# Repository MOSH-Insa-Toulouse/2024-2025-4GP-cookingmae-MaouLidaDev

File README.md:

# 2024-2025-4GP-cookingmae-MaouLidaDev

# SOMMAIRE
***
- [2024-2025-4GP-cookingmae-MaouLidaDev](#2024-2025-4gp-cookingmae-maoulidadev)
- [SOMMAIRE](#sommaire)
    - [But du projet](#but-du-projet)
    - [Livrables](#livrables)
    - [Matériel donnée](#matériel-donnée)
    - [Simulation du circuit sous Ltspice](#simulation-du-circuit-sous-ltspice)
    - [Création du Shield sous Kicad](#création-du-shield-sous-kicad)
    - [Code Arduino](#code-arduino)
    - [Application Android sous MIT App Inventor](#application-android-sous-mit-app-inventor)
    - [Banc de test](#banc-de-test)
    - [Datasheet](#datasheet)
    - [Conclusion](#conclusion)
    - [Contact](#contact)
***  

### But du projet

Le but du projet est de pouvoir venir comparer deux technologies de jauge de contrainte.
* Une jauge provenant du commerce : Un "flex sensor" ayant une résistance à plat d'environ 28KOhms
* Une jauge de contrainte en graphite faite par nos soins s'inscrivant dans le cadre des technologies low tech

Pour fabriquer notre jauge de contrainte low tech et low cost, nous nous basons sur un article scientifique intitulé: "Pencil Drawn Strain Gauges and Chemiresistors on Paper" publié par Cheng-Wei Lin, Zhibo Zhao, Jaemyung Kim et Jiaxing Huang dans lequel il a été prouvé que l'on puisse créer une jauge de contraite à partir d'une piste de graphite. Cette piste de graphite peut être dessiner à l'aide d'un crayon à papier sur une feuille de papier tout deux disponibles dans le commerce. En effet, en se basant sur les phénomènes de transport dans les systèmes granulaires, on peut observer une modification de la resistance de la piste en fonction de la flexion de cette dernière. Nous souhaitons observer ce phénomène pour differentes pistes de graphite plus au moins chargées en particles de graphite. Ainsi, nous pourrons étudier la variation de résistance de la piste en fonction de la déformation et ce pour chaque piste obtenue par dépot de crayon à papier differents.

Afin de pouvoir observer ce phénomène, nous avons débuté ce projet et proposons de répondre à la question suivante: "Est ce que la sensibilité d'une jauge de contrainte en graphite peut être comparable à celle d'une jauge dans le commerce et si oui est-il possible de commercialiser cette jauge low cost et low tech à grande echelle?"

Pour repondre à cette question, nous mettons en place un protocole constituer de phase de design, création, programmation et test pour notre jauge de contrainte en graphite.
Voici  un récapitulatif des étapes:
* Designer et créer un montage d'amplifaction nous permettant d'exploiter notre jauge en graphite et de relier sa sortie à une carte arduino
* Intégrer un potentiomètre digitale en entrée de notre montage d'amplifaction pour calibrer les mesures
* Créer un shield sous Kicad permettant d'y intégrer notre montage amplificateur, notre potentiomètre, nos 2 capteurs à comparer, un écran OLED pour voir la mesure que nous effectuons, un module Bluetooth pour exporter les datas vers un téléphone android et un encodeur rotatoire
* Préparer le PCB et y integrer tous les composants 
* Créer un code Arduino nous permettant de contrôler tous les éléments dont nous disposons sur notre PCB
* Tester notre code ainsi que notre montage physique 
* Tester les deux capteurs et recenser dans une datasheet les caractéristiques de notre jauge de contrainte low cost
* Répondre à la problèmatique concernant notre jauge de contrainte 
* Préparer nos splendides résultats durant une soutenance fin Mai

### Livrables

* Un shield PCB conçu sous Kicad pouvant se fixer à une carte Arduino UNO avec au-dessus un amplificateur transimpédance, un module Bluetooth, un écran OLED, un potentiomètre digital, un encodeur rotatoire, un Flex Sensor et notre capteur.
* Un code Arduino gérant la mesure de résistance d'une jauge de contrainte faite en graphite, la communication avec un module Bluetooth pour réceptionner les valeurs de la mesure sur un portable Android, l'affichage sur l'écran OLED d'actions possibles et la gestion du potentiomètre digital permettant la calibration de notre capteur.
* Un code Android APK qui gère l'interfaçage du système de mesure sur un téléphone Android.
* La datasheet du capteur de contrainte en graphite.

### Matériel donnée 

* 1 carte Arduino Uno
* 2 Résistance de 100kΩ
* 1 Résistance de 1kΩ
* 1 Potentiomètre digital MCP-41050
* 2 Condensateurs 100nF
* 1 Condensateurs 1µF
* 1 AOP LTC1050
* 1 Écran OLED01
* 1 Module Bluetooth HC-05

### Simulation du circuit sous Ltspice

Nous souhaitons pouvoir récupérer la resistance de notre capteur de Graphite. Ce dernier, lorsqu'une de ses pins est connectée à une source de tension d'environ 5V, délivre sur sa deuxième pin un très faible courant (de l'ordre du nanoampère). En effet, la résistance de notre jauge de contrainte en graphite est de l'ordre du gigaohm ce qui pour la gamme de tension d'alimentation dont nous disposons pour nos tests se traduit par un courant très faible à exploiter. 

Pour pouvoir tout de même récupérer la variation de resistance de notre capteur, nous proposon un montage d'amplification transimpédence composé de 3 filtres passe bas et d'un AOP. L'AOP amplifie notre signal pour atteindre une tension qui pourra ensuite être lue par une carte Arduino UNO. Nous avons choisi le LTC 1050.
En plus de l'AOP, nous rajoutons 3 filtres: 
  - Un filtre passe bas passif composé de R1 et C1 de fréquence de coupure de 16Hz pour filtrer les bruits en courant sur le signal d'entrée
  - Une filtre passe bas actif composé de R3 et C4 de fréquence de coupure de 1.6Hz permettane de filtre la composante de bruit à 50Hz provenant du couplage avec le réseau éléctrique 
  - Un filtre passe bas standard composé de R6 et C2 de fréquence de coupure de 1.6kHz qui permet de s'affranchir des bruit crées par l'environnement de l'observation
 Il est possible de venir rajouter une resistance variable R2 de sorte à pouvoir garantir la non saturation de l'entrée analogique de la carte Arduino UNO récupérant le signal de sortie de l'amplificateur transimpédance. En effet, comme la resistance de la piste varie en fonction de sa teneur en particule de graphite, il sera possible de venir faire varier R2 pour modifier le gain de notre amplification. 
 
 Nous avons testé ce montage sur le logiciel LTspice basé sur [ce schéma](https://github.com/MOSH-Insa-Toulouse/2024-2025-4GP-cookingmae-MaouLidaDev/blob/main/Images/SchemaLTSpice.png) 

Grâce à notre simulation, nous avons pu valider que nos filtres sont bien dimensionnés pour atténuer les bruits (par exemple, dans le cas des simulations en courant alternatif, on constate que notre atténuation est de l'orde 40dB pour la composante à 50Hz).

### Création du Shield sous Kicad

Voici ci-dessous des images des schéma de notre PCB sous Kicad: 

Le PCB a été entierement designé sous le logiciel Kicad et imprimé au sein de deux départements de l’INSA Toulouse, le Génie Électrique et Informatique et le Génie Physique. Il a été fabriqué avec une plaquette d’époxy recouverte d’une couche de cuivre d’environ 60𝝻m sur laquelle nous avons imprimé le circuit. Pour imprimé le circuit, nous utilisons un calque nous permettant d'isoler les pistes des UVs et de venir graver à l'aide d'un bain de percholorure de fer les parties en cuivre non désirées. 

Une fois le PCB tiré, nous sommes passé à la soudure des composants nécéssaires pour pouvoir analyser la réponse de notre capteur graphite. 
Voici ci-dessous une image de notre carte une fois imprimée et une fois tous les composants ajoutés: 

### Code Arduino 

Pour pouvez retrouver le code commenté permettant d'avoir la variation de résistance relative en fonction de la déformation [ici](https://github.com/MOSH-Insa-Toulouse/2024-2025-4GP-cookingmae-MaouLidaDev/blob/main/Arduino/Code_Arduino.ino)

Le but de ce code est de gérer l'acquisition des tensions en sortie de l'amplificateur et du Flex Sensor, ainsi que la calibration automatique du potentiomètre digital.

Lorsque le code est téléversé sur la carte Arduino, le programme attend que le début de l'acquisition soit enclenché par l'utilisateur sur l'application Android (mentionnée plus tard). Après cette première étape, il est possible de sélectionner plusieurs actions en tournant et en appuyant sur l'encodeur rotatoire :\
-Pause qui force le programme à ne rien faire;\
-Calibre A qui calibre le potentiomètre digital pour que la tension en sortie de l'AOP ne sature pas à 5V ou à 0V;\
-Mesure Flex qui récupère la valeur de la tension sur le Flex Sensor et la convertit en résistance, mesure envoyée à l'application Android sous forme de byte;\
-Mesure Capteur qui récupère la valeur de la tension en sortie de l'AOP et envoie la donnée à l'application Android sous forme de byte;

La fréquence d'échantillonage est de 2Hz (pour Mesure Flex et Capteur). Lors que l'action Calibre A est sélectionnée, le programme n'effectue que cette tâche et aucune autre fonction est activée. Cette calibration prend entre 5 et 10s.

### Application Android sous MIT App Inventor

Pour pouvoir récupérer la variation de la résistance en fonction de la déformation, nous avont créer une application pouvant communiquer avec le module Bluetooth présent sur notre PCB. Nous avons utilisé le site MIP App Inventor. 
Vous retrouverez notre application dans la séction dédiée. Nous avons : 

Le but de ce code est de gérer la réception des données et de leur affichage, ainsi que la calibration manuelle pour initialiser la résistance variable R2.

Lorsqu'on se connecte au module Bluetooth présent sur la PCB, on peut commencer l'acquisition des données. En fonction de l'action sélectionnée, on affiche sur la face-avant de l'application différentes informations. Si l'action sélectionée est :\
    -Pause, rien de nouveau s'affiche;\
    -Calibre A, il est nécéssaire d'appuyer sur le bouton "Calibration Automatique" pour récupérer la valeur de la résistance du potentiomètre digital. L'application reste figé et attend de recevoir de l'Arduino le byte associé au potentiomètre digital et affiche la valeur de la résistance et précise aussi que la calibration a été faite automatiquement;\
    -Mesure Flex, la valeur de la résistance est affiché dans un indicateur et sur un graphe pour suivre l'évolution de cette résistance. Il est nécessaire de placer le Switch du côté "Flex Sensor" pour avoir la bonne résistance du Flex Sensor;\
    -Mesure Capteur, la valeur de la résistance est affiché dans un indicateur et sur un graphe pour suivre l'évolution de cette résistance. Il est nécessaire de placer le Switch du côté "Capteur" pour avoir la bonne résistance du Capteur;

De plus, il est possible de rentrer manuellement la valeur de la résistance R2 si : la calibration automatique ne renvoie pas la bonne valeur mesurée sur le potentiomètre digital à l'aide d'un multimètre OU si on n'utilise pas de potentiomètre digital et qu'on le remplace simplement par une résistance. Enfin, il est possible d'arrêter l'acquisition des mesures et de la relancer, effaçant toutes les informations présentes sur le graphe et les indicateurs.

(Remarque : la fréquence du code Android est de 10Hz pour récupérer le byte de données associé aux résistances du Capteur et du Flex Sensor).

### Banc de test

Pour pouvoir compléter notre datasheet, nous devons évaluer les performances de notre capteur à travers un banc de test. Pour cela, nous utiliserons un demi cylindre à rayon variable dont nous connaissons préalablement le rayon de courbure: 

Ce banc de test a été imprimé en 3D et dispose de demis-cercles de rayons variant de 2cm à 4,5cm avec un pas de 0,5cm par demi cercle.  

Pour évaluer notre capteur en graphite, on veut pouvoir connaître la variation de résistance relative du capteur en fonction de la déformation subie. Nous notons la variation de résistance relative: $\frac{\Delta R}{R_0}$  et la déformation:  $\epsilon=\frac{e}{D}$ avec ${e}$ l'épaisseur de notre papier que l'on a mesurée à e=0.2mm et ${D}$ le diamètre du cercle choisit. Il est ainsi aisé de determiner la déformation associée à chaque demi-cercle et il ne reste plus que à mesurer la résistance ${R_0}$ de notre capteur au repos et la variation de résistance de ce dernier lorsqu'on vient le plaquer contre les différents demis-cercles. 

Nous souhaitions originalement utiliser cette méthode qui nous a été suggerée en cours mais il a été compliqué pour nous de la mettre en oeuvre. En effet, nous n'avions pas assez de variation en résistance pour les différents diamétres testés. Cela est peut être dû à un mauvais réglage du potentiomètre digitale ne nous permettant pas d'exploiter la sensibilité de la jauge. Nous passons à un test plus "rudimentaire" se basant sur le même principe mais sur lequel nous contrôlons cette fois l'angle d'inflexion (en rad) de la jauge. On a donc  $R=\frac{D}{2}=\frac{L}{\theta}$ avec L la longueur de notre jauge mesurée à L=3.8cm
Au final on peut écrire la déformation:  $\epsilon=\frac{e\theta}{2L}$

On obtient ainsi la courbe de la variation de résistance en fonction de la déformation. Nous testons notre capteur pour differentes compositions en particule de graphite en compression et aussi en tension. On note que lorsque la déformation est positive c'est que nous étudions la compression (l'angle de courbure est compté positif) alors que lorsqu'elle est négative c'est que nous étudions la tension (l'angle de courbure est compté négatif). 
Nous obtenons: 

De même, nous pouvons établir uniquement en tension cette fois ($\epsilon$ < 0), la courbe de variation de resistance du capteur commercial : "le flex sensor". Nous obtenons: 

De nos observations, on constate que la résistance diminue lorsque nous sommes en compression, ce qui est normal car les particules de graphites se rapprochent les unes des autres et permettent une meilleure conductivité. Logiquement, en tension, la résistance augmente puisque qu'on rend la distance entre chaque particule de graphite beaucoup plus grande. 
On constate aussi que ces variations de résistance dépendent beaucoup du niveau de gras du grain en graphite que nous avons utilisé pour notre jauge. Lorsque notre crayon comporte beaucoup de graphite (2B ou B), la variation relative de resistance est plus importante. Lorsque notre crayon est plus dur (HB 2H avec beaucoup d'argile et moins de graphite) la resistance à plat est plus importante et nous avons une variation relative de resistance moins importante.  

NB: Il y'a certaines zones d'incertitudes à prendre en compte lors de l'analyses des performances de nos capteurs. En effet, entre chaque capteur testé, il est impossible d'estimer réellement la quantité de graphite déposée. De plus, il est difficile d'estimer si le banc de test élaboré permet de tester sans dégrader la qualité de nos capteurs. Il serait ainsi intéressant d'élaborer un nouveau banc de test utilisant un servo-moteur. 

### Datasheet 

Pour pouvez retrouver la datasheet [ici](https://github.com/MOSH-Insa-Toulouse/2024-2025-4GP-cookingmae-MaouLidaDev/blob/main/Datasheet/Datasheet_capteur_2025.pptx)

### Conclusion

Le but de ce projet était de venir comparer une technologie de jauge de contrainte commerciale: "Flex sensor" avec une jauge de contrainte facilement reproductible et low cost en graphite se basant sur l'article : "Pencil Drawn Strain Gauges and Chemiresistors on Paper" publié par Cheng-Wei Lin, Zhibo Zhao, Jaemyung Kim et Jiaxing Huang.  

Notre problématique était la suivante: "Est ce que la sensibilité d'une jauge de contrainte en graphite peut être comparable à celle d'une jauge dans le commerce et si oui est-il possible de commercialiser cette jauge low cost et low tech à grande échelle?"

--> Notre jauge de contrainte en graphite permet en effet d'observer une variation de résistance en fonction de la déformation et assure donc sa mission de base. On peut appliquer sur nos jauges des tensions mais aussi des compressions ce qui n'est pas possible pour le capteur commercial Flex sensor dont nous disposons. Nos jauges en graphite permettent de plus grande variations de résistance que le flex sensor mais elles restent tout de même moins sensibles. Nous avons du mal à évaluer la flexion maximale que nous pouvons appliquer sur nos jauges donc nous ne pouvons pas déterminer si nous les cassons en cours d'expérimentation. Le flex sensor semble alors plus robuste et plus précis. 
Pour conclure, nos jauges en graphite low tech permettent d'avoir une idée sur la déformation grâce à une variation relative, ils sont faciles à produire et permettent d'exploiter le phénomène de conduction dans les systèmes granulaires et c'est assez cool! En revanche, ses performances sont limitées et sa sensibilité ne permet pas d'avoir des résultats similaires à ce qui se fait sur le marché. 

--> En ce qui concerne la commercialisation de notre capteur, nous venons de voir que les performances de notre jauges ne sont pas comparables à ce qui se fait sur le marché actuellement mais peut tout de même dépané et permettre de se faire une idée de la déformation. Malheureusement, nos conditions de test étant assez rudimentaires, nous ne pouvons pas attester de la qualité de notre produit. Afin de pouvoir pleinement répondre à cette question, il faudrait mener des tests plus reproductibles, plus en profondeur pour pouvoir atteindre de meilleures performances. 

### Contact

-Hamadi Maoulida: mhamadi@insa-toulouse.fr  
-Tartera Maëlys : tartera@insa-toulouse.fr

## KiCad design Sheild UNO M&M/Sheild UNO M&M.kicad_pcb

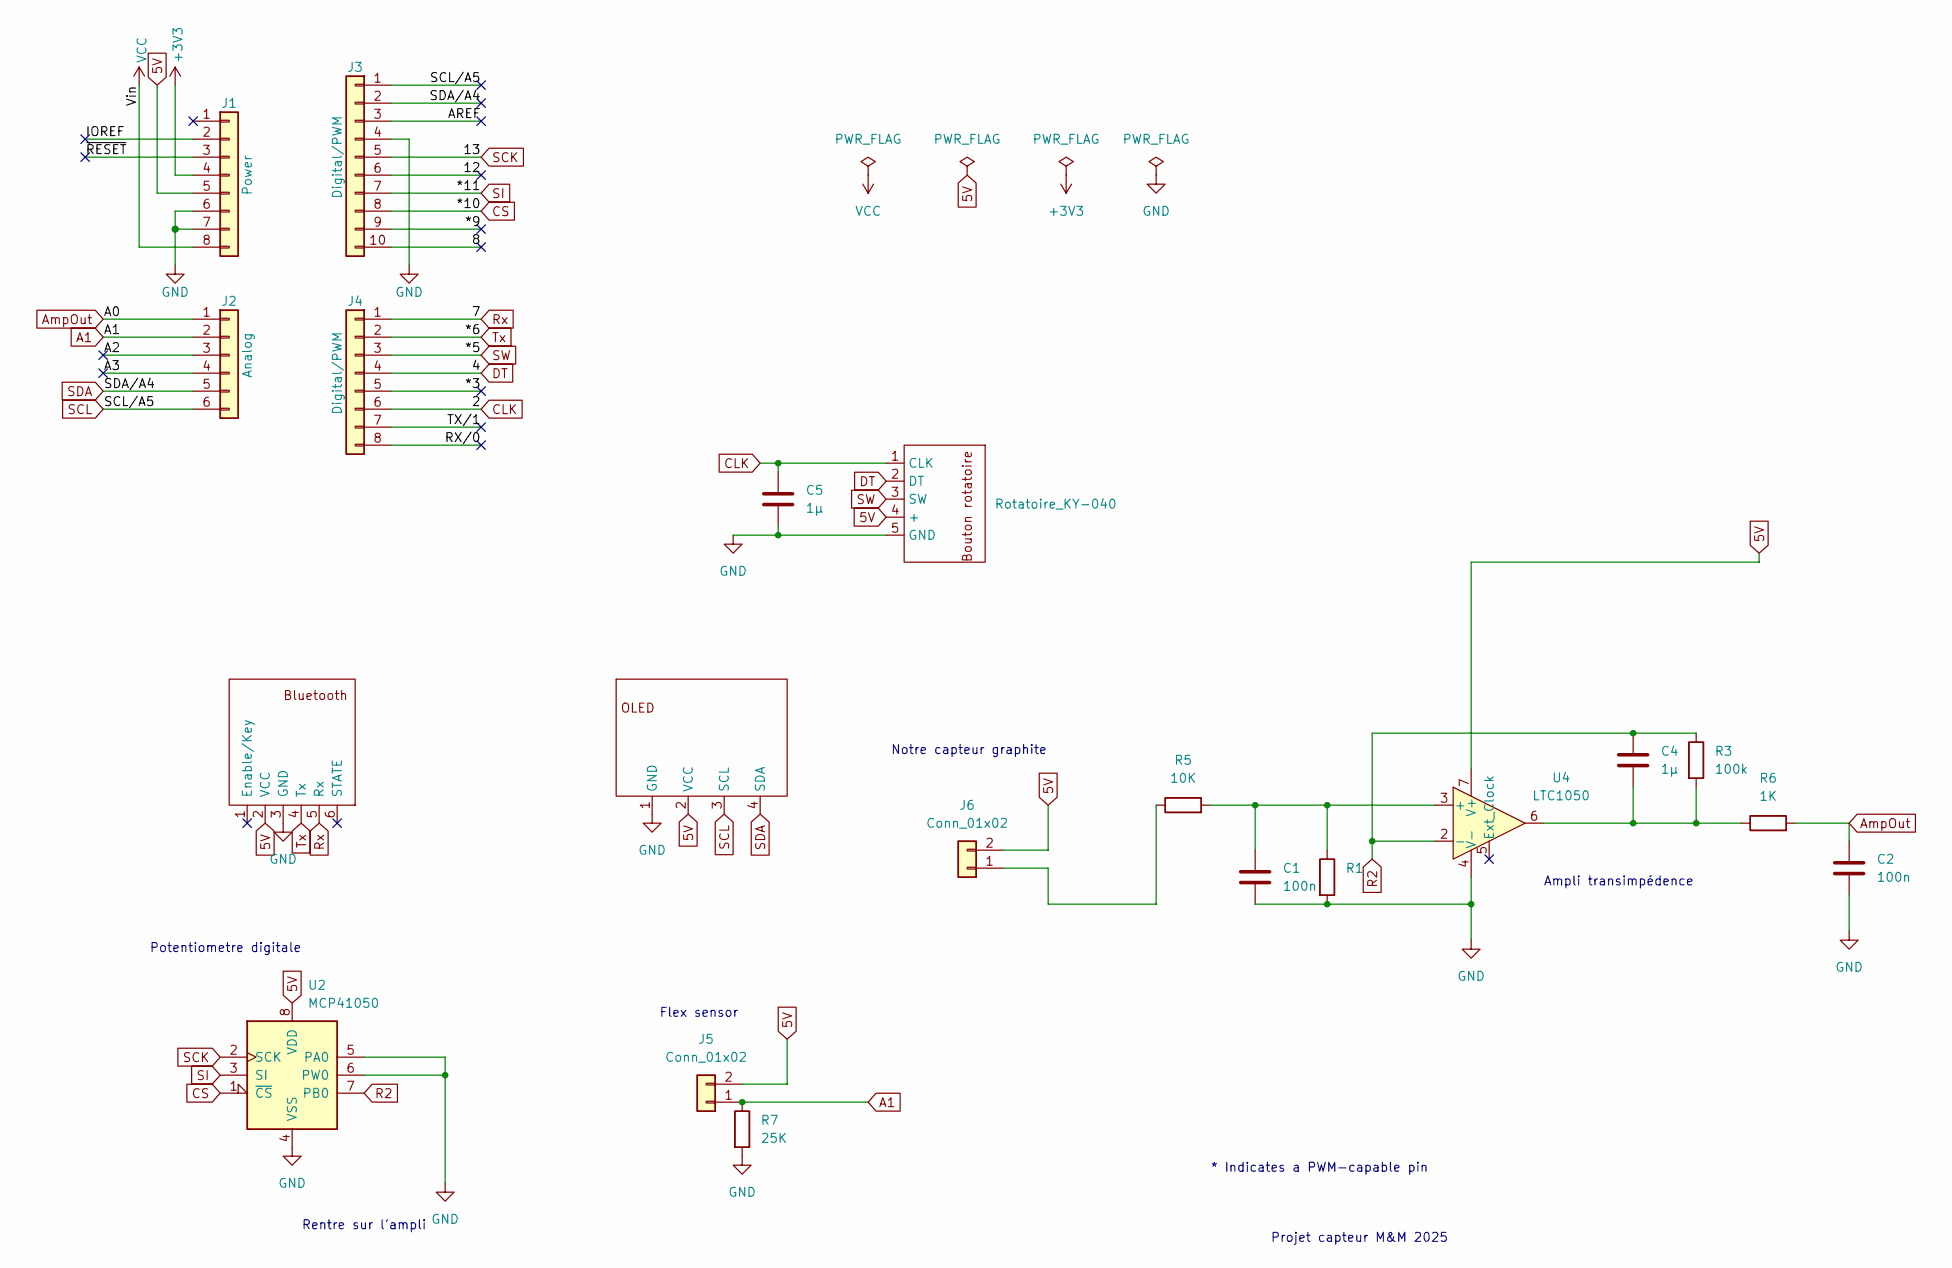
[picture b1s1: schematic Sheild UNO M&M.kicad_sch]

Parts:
1: Rotatoire_KY-040; Rotatoire_KEY-040_Empreinte
C1, C2: 100n; C_Disc_D6.0mm_W4.4mm_P5.00mm_Capa_100n_Empreinte
C4, C5: 1µ; C_Rect_L7.0mm_W4.5mm_P5.00mm_Capa_1µ_Empreinte
DS1: OLED; Oled_Empreinte
J1: Power; PinSocket_1x08_P2.54mm_Vertical
J2: Analog; PinSocket_1x06_P2.54mm_Vertical
J3: Digital/PWM; PinSocket_1x10_P2.54mm_Vertical
J4: Digital/PWM; PinSocket_1x08_P2.54mm_Vertical
J5, J6: Conn_01x02; PinSocket_1x02_P2.54mm_Vertical_Modifié
R1, R3: 100k; Resistance_Empreinte
R5: 10K; Resistance_Empreinte
R6: 1K; Resistance_Empreinte
R7: 25K; Resistance_Empreinte
U1: HC05; Blutooth_Empreinte
U2: MCP41050; Potentiometre MCP41050
U4: LTC1050; Potentiometre MCP41050

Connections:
5V: 1.4 (+), DS1.2 (VCC), J1.5, J5.2, J6.2, U1.2 (VCC), U2.8 (VDD), U4.7 (V+)
+3V3: J1.4
/8: J3.10
/12: J3.6
/*3: J4.5
/*9: J3.9
/A2: J2.3
/A3: J2.4
/AREF: J3.3
/IOREF: J1.2
/RX/0: J4.8
/TX/1: J4.7
/~RESET: J1.3
A1: J2.2, J5.1, R7.1
AmpOut: C2.1, J2.1, R6.2
CLK: 1.1 (CLK), C5.1, J4.6
CS: J3.8, U2.1 (~CS)
DT: 1.2 (DT), J4.4
GND: 1.5 (GND), C1.2, C2.2, C5.2, DS1.1 (GND), J1.6, J1.7, J3.4, R1.2, R7.2, U1.3 (GND), U2.4 (VSS), U2.5 (PA0), U2.6 (PW0), U4.4 (V-)
unnamed: C4.2, R3.2, R6.1, U4.6
unnamed: J6.1, R5.1
unnamed: C1.1, R1.1, R5.2, U4.3 (+)
R2: C4.1, R3.1, U2.7 (PB0), U4.2 (-)
Rx: J4.1, U1.5 (Rx)
SCK: J3.5, U2.2 (SCK)
SCL: DS1.3 (SCL), J2.6, J3.1
SDA: DS1.4 (SDA), J2.5, J3.2
SI: J3.7, U2.3 (SI)
SW: 1.3 (SW), J4.3
Tx: J4.2, U1.4 (Tx)
VCC: J1.8

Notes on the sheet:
Potentiometre digitale
Flex sensor
Projet capteur M&M 2025
Rentre sur l'ampli
* Indicates a PWM-capable pin
Ampli transimpédence
Notre capteur graphite

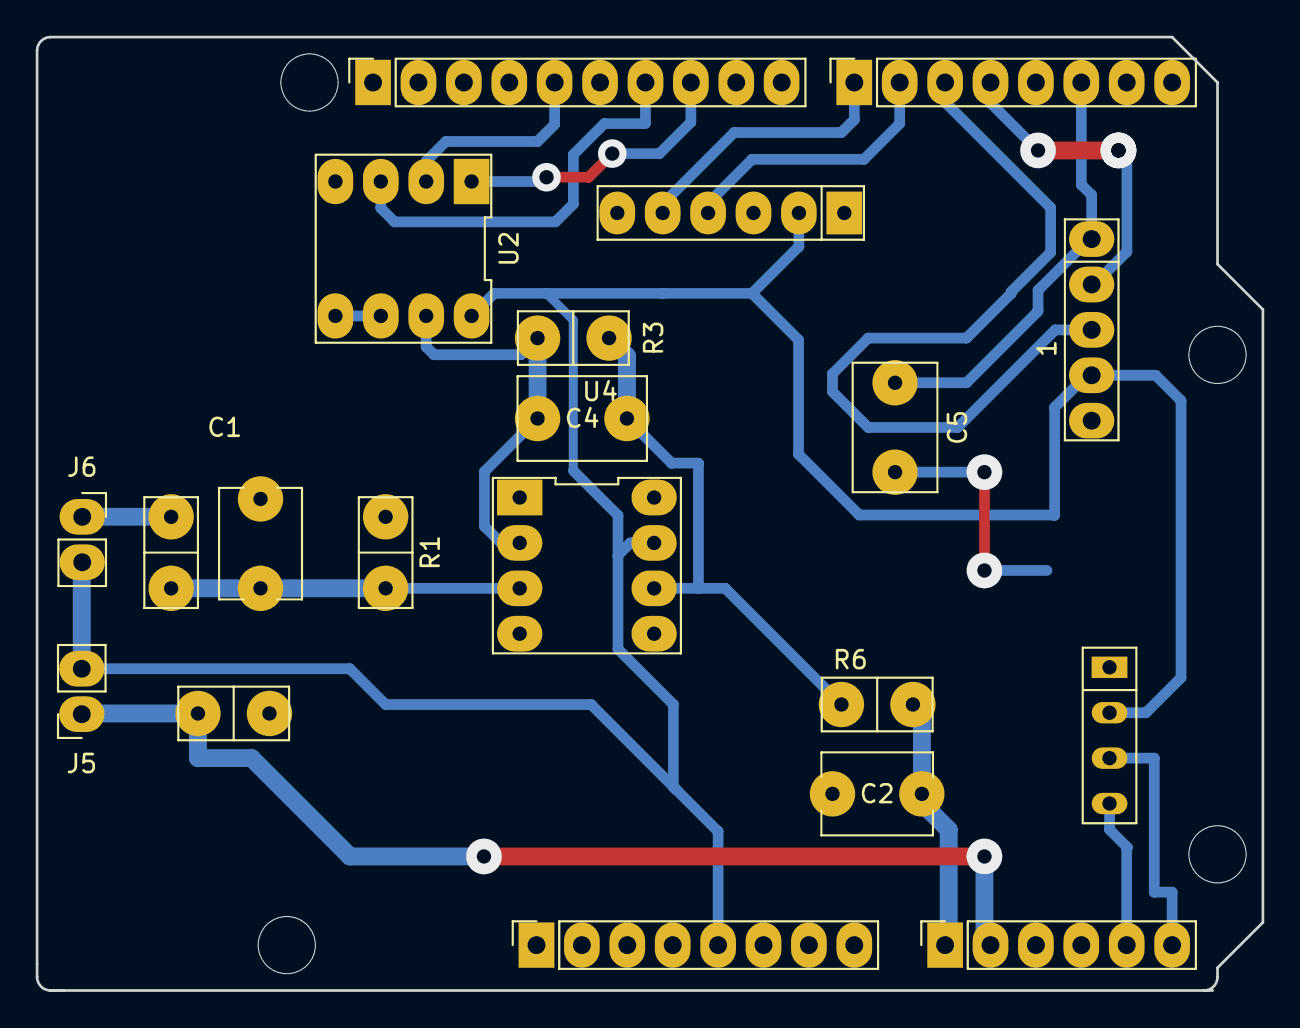
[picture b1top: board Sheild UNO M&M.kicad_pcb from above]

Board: 2 copper layers, 68.6 x 53.3 mm, 24 parts (0 on the bottom side), 18 nets.

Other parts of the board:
MH1, MH2, MH3, MH4: MountingHole_3.2mm

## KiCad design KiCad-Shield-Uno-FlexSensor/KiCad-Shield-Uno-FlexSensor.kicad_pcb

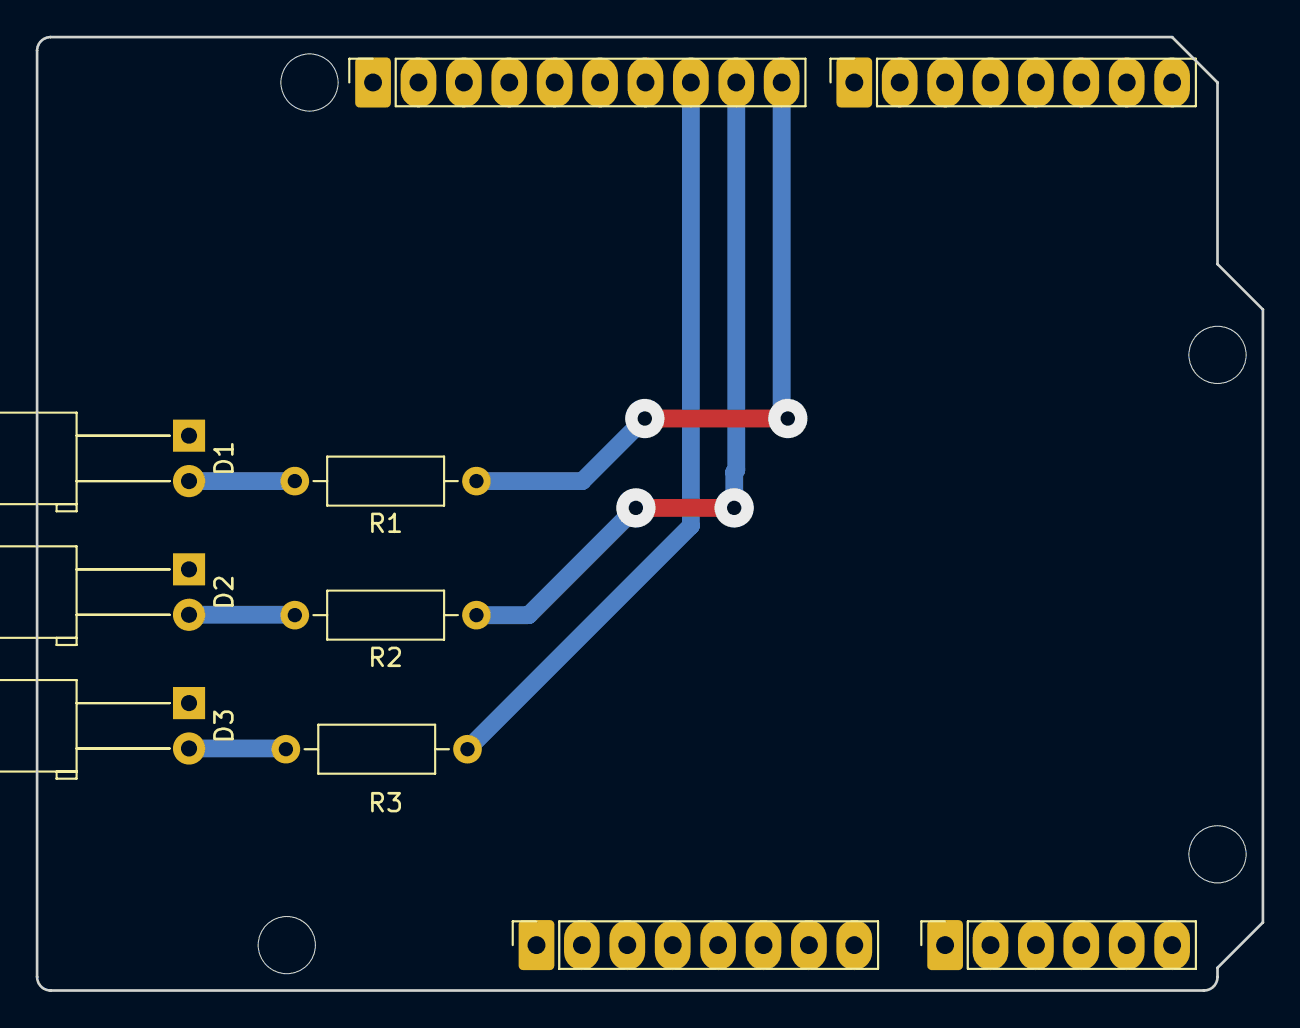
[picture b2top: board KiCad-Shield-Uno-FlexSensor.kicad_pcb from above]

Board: 2 copper layers, 68.6 x 53.3 mm, 14 parts (0 on the bottom side), 7 nets.

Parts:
D1: STAT; LED_D5.0mm_Horizontal_O6.35mm_Z3.0mm
D2: MODE; LED_D5.0mm_Horizontal_O6.35mm_Z3.0mm
D3: ERR; LED_D5.0mm_Horizontal_O6.35mm_Z3.0mm
J1: Power; PinSocket_1x08_P2.54mm_Vertical
J2: Digital/PWM; PinSocket_1x10_P2.54mm_Vertical
J3: Analog; PinSocket_1x06_P2.54mm_Vertical
J4: Digital/PWM; PinSocket_1x08_P2.54mm_Vertical
MH1, MH2, MH3, MH4: MountingHole_3.2mm
R1, R2, R3: 680; R_Axial_DIN0207_L6.3mm_D2.5mm_P10.16mm_Horizontal

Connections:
/D8: J2.10, R1.1
/D9: J2.9, R2.1
/D10: J2.8, R3.1
GND: D1.1 (K), D2.1 (K), D3.1 (K), J1.6, J1.7, J2.4
unnamed: D1.2 (A), R1.2
unnamed: D2.2 (A), R2.2
unnamed: D3.2 (A), R3.2

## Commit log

2025-02-21 Ajout de ma to-do list
2025-02-21 Ajout d'un item à ma liste
2025-02-21 modification de la liste
2025-02-21 Modif de la ligne 5 du fichier READMEE
2025-02-21 Rajout d'une virgule
2025-02-21 J'ai aussi modifie la ligne 5 ahah
2025-02-21 Mae casse tout
2025-02-21 C'est moi qui ait raison
2025-02-21 Raison
2025-02-21 modified: README.md
2025-03-10 Compléter le readme avec des informations complémentaires sur le cahier des charges et le matériel requis
2025-03-10 Compléter readme avec des sous sections pour placer les attentes du projet
2025-03-15 Effacer le shield qui ne marche pas
2025-03-15 Rajout du shiel qui n'est pas encore finis avec les empreintes et le début du routage
2025-03-15 Correction de l'erreur du GND connecté au 5V, continuer le routage
2025-03-15 Rajout de nos noms sur le shield
2025-03-15 Rajout des simulations LTSpice
2025-03-16 Corrections PCB sur les empreintes des connecteurs et amélioration des via
2025-03-18 Correction PCB et ajout des modèles 3D
2025-03-18 Rajout du code arduino
2025-03-18 Rajout d'un dossier d'image parce que pourquoi pas?
2025-03-18 Retrait de certaines fonctions Gestion pour les intégrer dans deux grandes fonctions Mesure
2025-03-18 Finalisation du shield
2025-03-18 Rajout du Gerber
2025-03-25 Rajout d'une image de la simulation du LTSpice
2025-03-25 En train de compléter le ReadMe sur la partie de la simulation du LTSpice
2025-03-28 Création du fichier datasheet
2025-03-28 Modification datasheet
2025-03-28 Datasheet complétée à 85%, manque les mesures et reste un paragraphe à rédiger
2025-03-29 Rajout d'images du banc de test, Rajout texte de fin de la datasheet, Rajout d'un sommaire sur le ReadME
2025-03-29 Test ReadME sommaire
2025-03-29 Sommaire
2025-03-29 Compléter le README avec les informations que nous avons déjà finis
2025-04-04 Compléter le README avec des éléments pour la conclusion et la banc de test, il ne reste plus que les valeurs!!
2025-04-11 Upload d'image
2025-04-11 Rajout images sur le README
2025-05-19 Modification Readme banc de test
2025-05-19 Correction affichage
2025-05-19 correction formule readme
2025-05-19 Rajout des courbes!
2025-05-19 Ajout des courbes dans le readme
2025-05-19 Modification readme
2025-05-19 Conclu
2025-05-20 Finir datahsheet
2025-05-20 Rajout de nouvelles courbes
2025-05-20 Modificatioin conclusion
2025-05-20 Modification de la datasheet
2025-05-20 Changement image
2025-05-20 Modification image
2025-05-20 Modification une ligne de la datasheet
2025-05-20 Code Arduino Final
2025-05-20 Code Android Final
2025-05-20 Faces avant et arrière de l'application Android
2025-05-21 Menage
2025-05-21 Rajout image apk
2025-05-21 Rajout code arduino
2025-05-21 Modif
2025-05-23 Modification datasheet et code
2025-05-29 Update README.md
    Ajout d'une explication du code Arduino et Android
2025-05-29 Update README.md
    Mise en forme
2025-05-29 Update README.md
    Mise en forme v2
2025-05-29 Update README.md
    Corrections des fautes d'orthographe
